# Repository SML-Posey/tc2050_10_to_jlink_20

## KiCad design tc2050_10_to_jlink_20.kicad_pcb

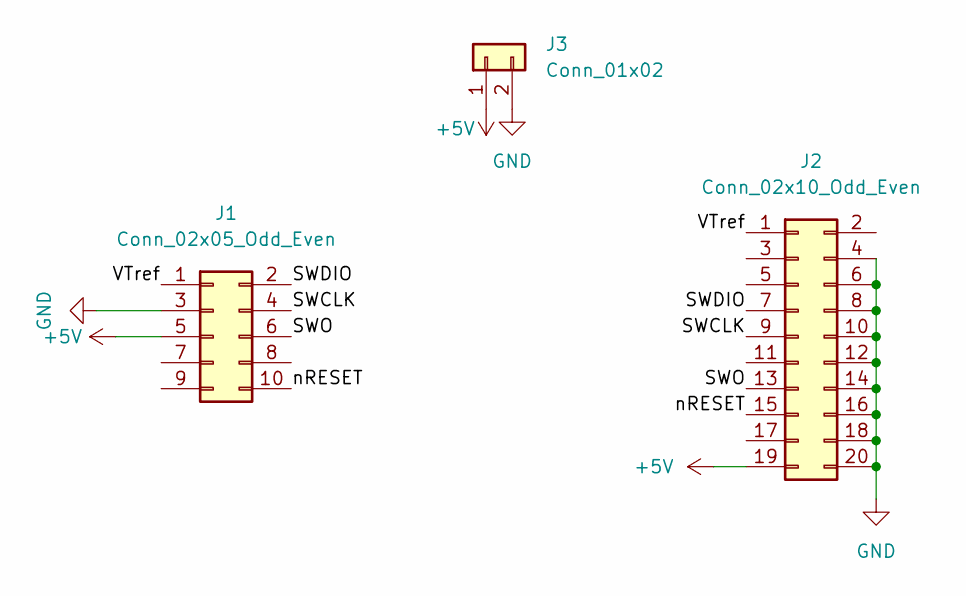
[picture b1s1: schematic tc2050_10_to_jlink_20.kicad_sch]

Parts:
J1: Conn_02x05_Odd_Even; IDC-Header_2x05_P2.54mm_Vertical
J2: Conn_02x10_Odd_Even; IDC-Header_2x10_P2.54mm_Horizontal
J3: Conn_01x02; PinSocket_1x02_P2.54mm_Vertical

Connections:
+5V: J1.5, J2.19, J3.1
/SWCLK: J1.4, J2.9
/SWDIO: J1.2, J2.7
/SWO: J1.6, J2.13
/VTref: J1.1, J2.1
/nRESET: J1.10, J2.15
GND: J1.3, J2.4, J2.6, J2.8, J2.10, J2.12, J2.14, J2.16, J2.18, J2.20, J3.2

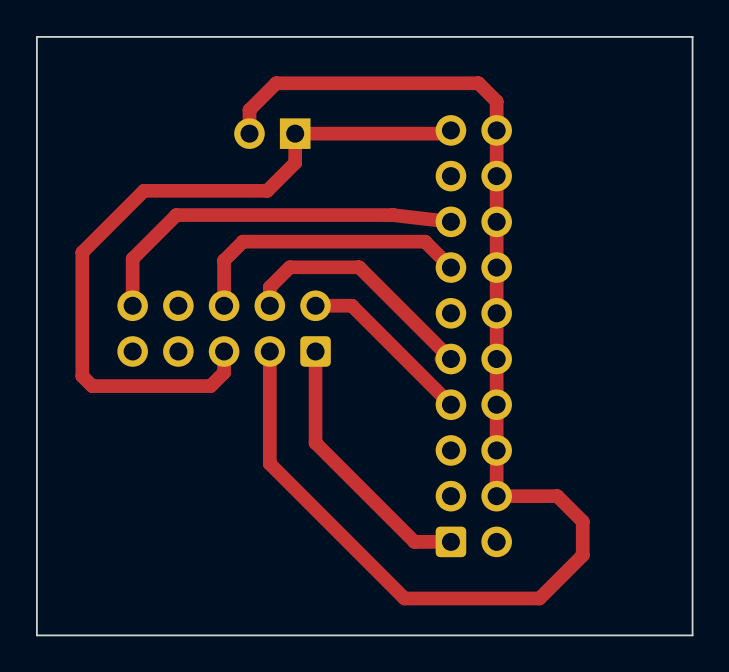
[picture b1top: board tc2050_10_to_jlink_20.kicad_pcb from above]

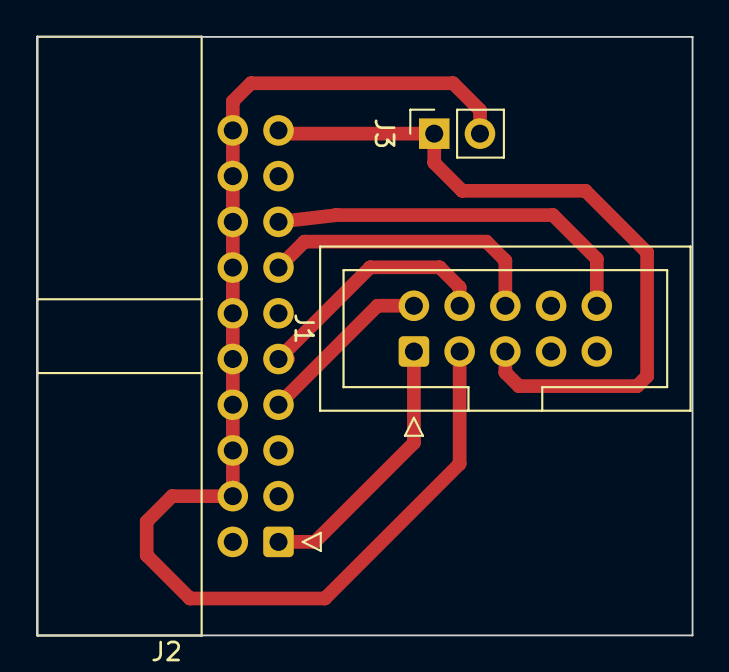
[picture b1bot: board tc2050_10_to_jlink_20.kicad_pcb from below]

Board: 2 copper layers, 36.4 x 33.2 mm, 3 parts (3 on the bottom side), 7 nets.

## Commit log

2023-03-15 v1, compatible with v8.1, r2.1, h1
